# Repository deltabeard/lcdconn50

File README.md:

# lcdconn50

## Note: Don't use this just yet! It has a lot of issues.

Raspberry Pi Breakout Board for a 50 Pin LCD Connector ([KD026
FM](http://www.startek-lcd.com/res/starteklcd/pdres/201303/20130329093105640.pdf)).

Uses CC-BY-SA-4.0 license. See the LICENSE file for more information.

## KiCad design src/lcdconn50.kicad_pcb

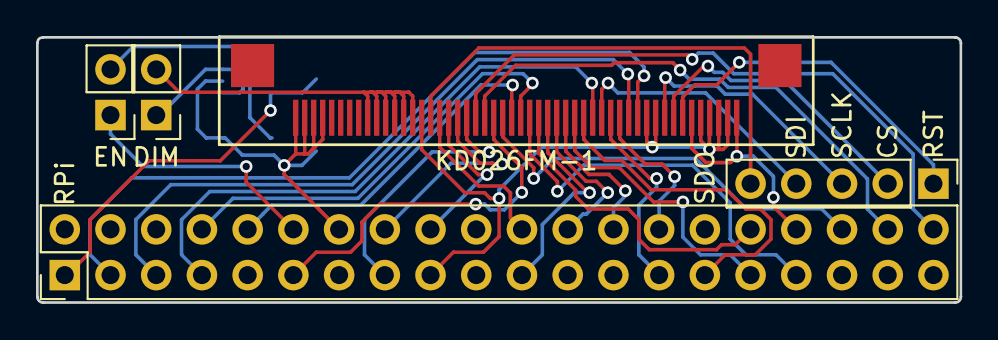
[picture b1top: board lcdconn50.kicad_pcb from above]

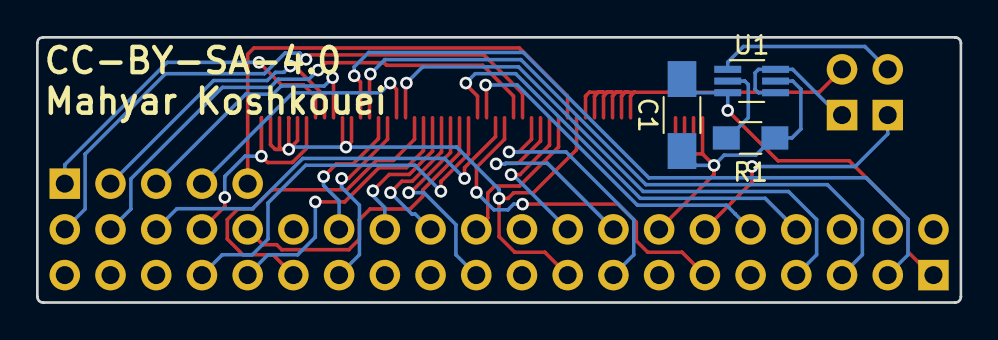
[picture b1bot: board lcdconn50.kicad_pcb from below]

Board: 2 copper layers, 51.3 x 14.7 mm, 8 parts (3 on the bottom side), 35 nets.

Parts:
C1: 1u; C_1206_HandSoldering
DIM: LEDs; Pin_Header_Straight_1x02_Pitch2.54mm
EN: DIMMER; Pin_Header_Straight_1x02_Pitch2.54mm
KD026FM-1: 2.6FM_1_PIN; FPC_50
R1: 1.5k; R_0805_HandSoldering
RPi: CONN_02X20; Pin_Header_Straight_2x20_Pitch2.54mm
SPI: SPI; Pin_Header_Straight_1x05_Pitch2.54mm
U1: CAT4002; SOT-363_SC-70-6_Handsoldering

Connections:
+3V3: C1.1, KD026FM-1.2, KD026FM-1.3, KD026FM-1.4, KD026FM-1.5, KD026FM-1.10, KD026FM-1.11, KD026FM-1.36, RPi.1, RPi.17, U1.3
+5V: RPi.2, RPi.4
/BCM_0: KD026FM-1.15, RPi.27
/BCM_1: KD026FM-1.14, RPi.28
/BCM_2: KD026FM-1.12, RPi.3
/BCM_3: KD026FM-1.13, RPi.5
/BCM_4: KD026FM-1.17, RPi.7
/BCM_5: KD026FM-1.18, RPi.29
/BCM_6: KD026FM-1.19, RPi.31
/BCM_7: KD026FM-1.20, RPi.26
/BCM_8: KD026FM-1.21, RPi.24
/BCM_9: KD026FM-1.22, RPi.21
/BCM_12: KD026FM-1.23, RPi.32
/BCM_13: KD026FM-1.24, RPi.33
/BCM_14: KD026FM-1.25, RPi.8
/BCM_15: KD026FM-1.26, RPi.10
/BCM_16: KD026FM-1.27, RPi.36
/BCM_17: KD026FM-1.28, RPi.11
/BCM_20: KD026FM-1.29, RPi.38
/BCM_21: KD026FM-1.30, RPi.40
/BCM_22: KD026FM-1.31, RPi.15
/BCM_23: KD026FM-1.32, RPi.16
/BCM_24: KD026FM-1.33, RPi.18
/BCM_25: KD026FM-1.34, RPi.22
BCM_18: EN.1, RPi.12
CS: KD026FM-1.8, SPI.2
GND: C1.2, KD026FM-1.1, KD026FM-1.6, KD026FM-1.47, KD026FM-1.48, KD026FM-1.49, KD026FM-1.50, R1.2, RPi.6, RPi.9, RPi.14, RPi.20, RPi.25, RPi.30, RPi.34, RPi.39, U1.5
unnamed: EN.2, U1.1
unnamed: DIM.1, U1.4, U1.6
unnamed: DIM.2, KD026FM-1.37, KD026FM-1.38, KD026FM-1.39, KD026FM-1.40, KD026FM-1.41, KD026FM-1.42
unnamed: R1.1, U1.2
RESET: KD026FM-1.7, SPI.1
SCLK: KD026FM-1.9, SPI.3
SDI: KD026FM-1.16, SPI.4
SDO: KD026FM-1.35, SPI.5

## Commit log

2017-06-23 Add Licence
2017-06-23 Finish circuit, placement, routing
    Additionally added footprint for [FPC
    connector](http://docs-europe.electrocomponents.com/webdocs/1282/0900766b81282588.pdf)
2017-06-24 Finish Routing
    Additionally added preview image.
2017-06-24 New Release
    Minor change to BCM_12 net.
    Updated Image.
